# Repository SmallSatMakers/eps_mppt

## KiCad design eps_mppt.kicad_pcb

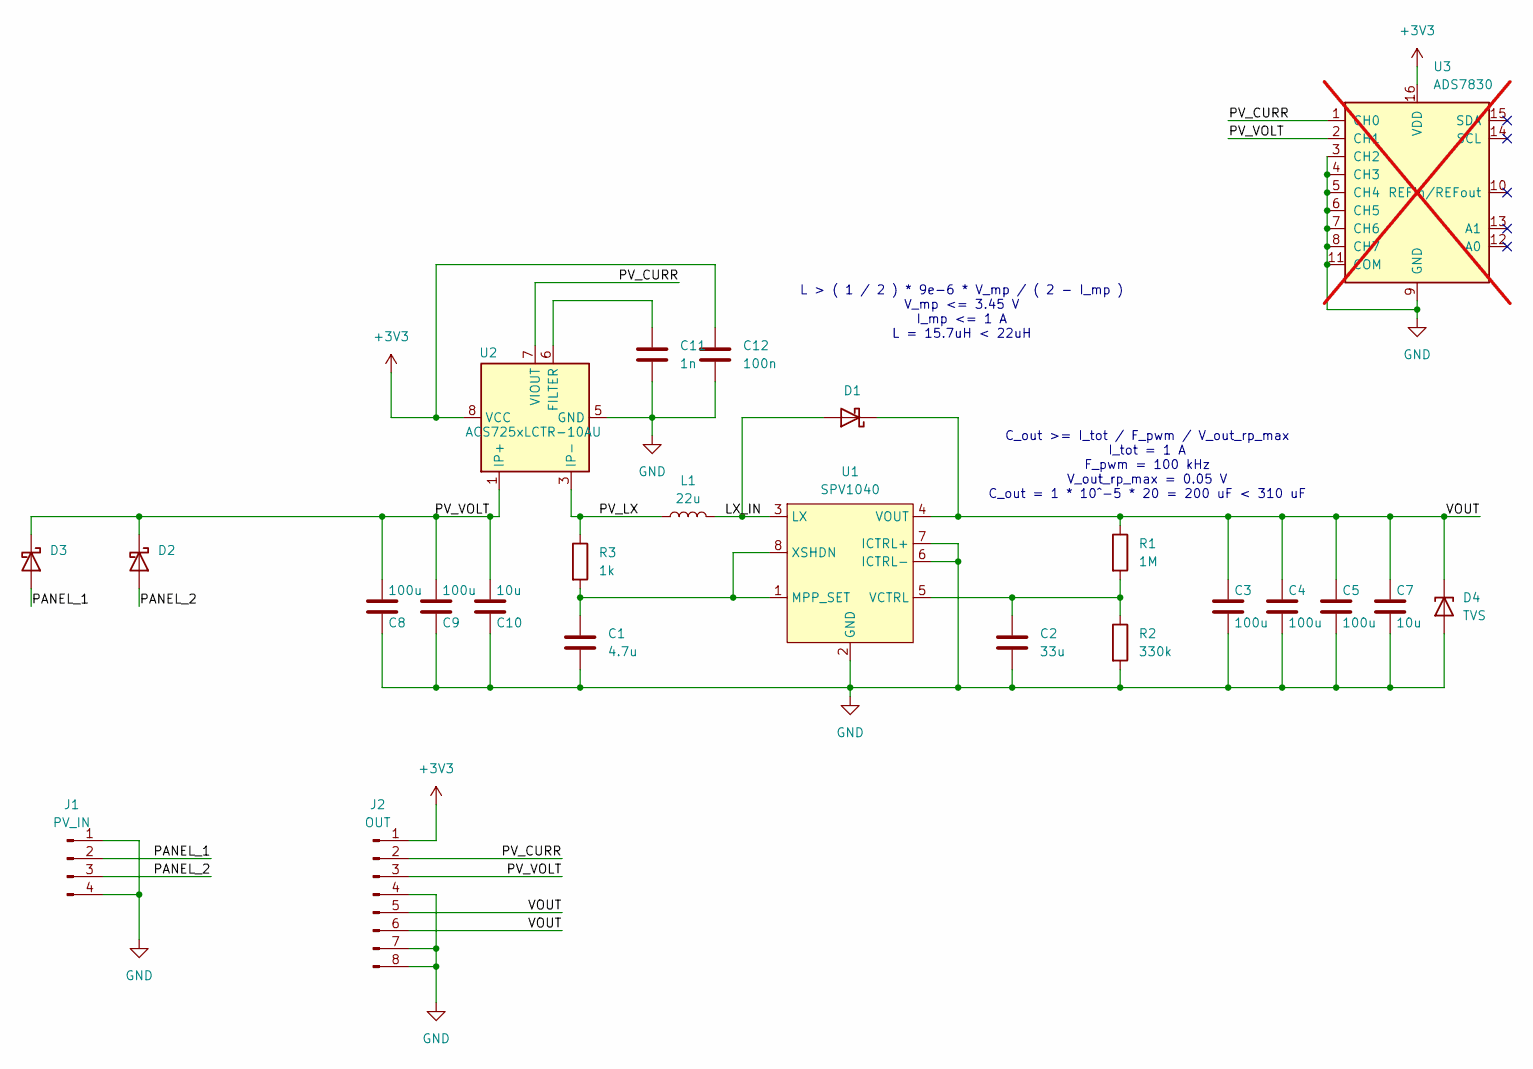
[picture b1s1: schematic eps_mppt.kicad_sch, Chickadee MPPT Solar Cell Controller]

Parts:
C1: 4.7u; C_0402_1005Metric
C2: 33u; C_0805_2012Metric
C3, C4, C5, C8, C9: 100u; C_1210_3225Metric
C7, C10: 10u; C_1206_3216Metric
C11: 1n; C_0402_1005Metric
C12: 100n; C_0402_1005Metric
D1, D2, D3: PD3S220L-7; PD3S220L7
D4: TVS; DO222-AA_STM
J1: PV_IN; PinHeader_1x04_P2.54mm_Vertical
J2: OUT; PinHeader_1x08_P2.54mm_Vertical
L1: 22u; L_Bourns_SRP5030T; Mfg. Part No. SRP5030WA-220M
R1: 1M; R_0603_1608Metric
R2: 330k; R_0402_1005Metric
R3: 1k; C_0402_1005Metric
U1: SPV1040; TSSOP-8_4.4x3mm_P0.65mm
U2: ACS725xLCTR-10AU; SOIC-8_3.9x4.9mm_P1.27mm
U3: ADS7830; TSSOP-16_4.4x5mm_P0.65mm; not fitted

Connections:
+3V3: C12.1, J2.1, U2.8 (VCC), U3.16 (VDD)
/LX_IN: D1.2 (A), L1.2, U1.3 (LX)
/PANEL_1: D3.2 (A), J1.2
/PANEL_2: D2.2 (A), J1.3
/PV_CURR: J2.2, U2.7 (VIOUT), U3.1 (CH0)
/PV_LX: L1.1, R3.1, U2.3 (IP-), U2.4 (IP-)
/PV_VOLT: C8.2, C9.2, C10.2, D2.1 (K), D3.1 (K), J2.3, U2.1 (IP+), U2.2 (IP+), U3.2 (CH1)
/VOUT: C3.1, C4.1, C5.1, C7.1, D1.1 (K), D4.1 (K), J2.5, J2.6, R1.1, U1.4 (VOUT)
GND: C1.2, C2.2, C3.2, C4.2, C5.2, C7.2, C8.1, C9.1, C10.1, C11.2, C12.2, D4.2 (A), J1.1, J1.4, J2.4, J2.7, J2.8, R2.2, U1.2 (GND), U1.6 (ICTRL-), U1.7 (ICTRL+), U2.5 (GND), U3.3 (CH2), U3.4 (CH3), U3.5 (CH4), U3.6 (CH5), U3.7 (CH6), U3.8 (CH7), U3.9 (GND), U3.11 (COM)
unnamed: C1.1, R3.2, U1.1 (MPP_SET), U1.8 (XSHDN)
unnamed: C2.1, R1.2, R2.1, U1.5 (VCTRL)
unnamed: C11.1, U2.6 (FILTER)

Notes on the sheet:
L > ( 1 / 2 ) * 9e-6 * V_mp / ( 2 - I_mp ) V_mp <= 3.45 V I_mp <= 1 A L = 15.7uH < 22uH
C_out >= I_tot / F_pwm / V_out_rp_max I_tot = 1 A F_pwm = 100 kHz V_out_rp_max = 0.05 V C_out = 1 * 10^-5 * 20 = 200 uF < 310 uF

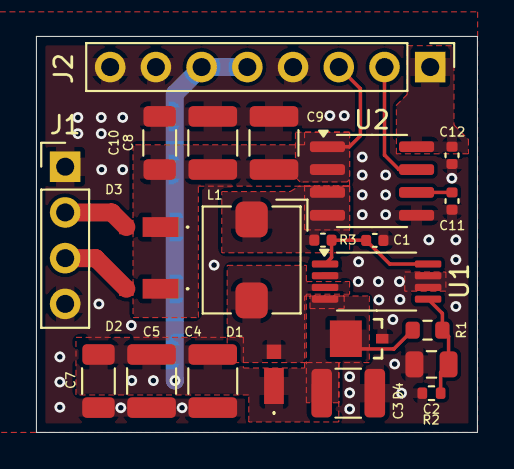
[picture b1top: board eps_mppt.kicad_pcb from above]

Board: 2 copper layers, 24.5 x 22.0 mm, 23 parts (0 on the bottom side), 12 nets.

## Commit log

2024-05-10 MPPT Controller Rev. 0
2024-05-14 Tweaked layout
2024-05-17 Optimized layout, truncated board
2024-05-17 Copper fill optimization
2024-05-17 Added BOM
2024-05-17 Updated BOM qty
2024-05-17 Further optimized layout to have better inductor path
2024-05-29 Updated BOM
